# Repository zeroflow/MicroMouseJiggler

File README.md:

# MicroMouseJiggler
Arduino Pro Micro based mouse jiggler.

It's simple.

It has a button.
You push the button, it starts periodically jiggling your mouse cursor.
You push the button again, it stops jiggling your mouse cursor.

The button glows green when active, and flashes when moving the cursor.
If it's not active, the button glows red, but turns off after a minute.

The PCB is designed to be soldered on top of an Arduino Pro Micro.
To have an easy illuminated button, the lever is illuminated from below by a neopixel LED.

All pieces are designed with 3D printing in mind, but the tolerances are chosen very low for a good fit.

CAD source: https://a360.co/3dbTGTp

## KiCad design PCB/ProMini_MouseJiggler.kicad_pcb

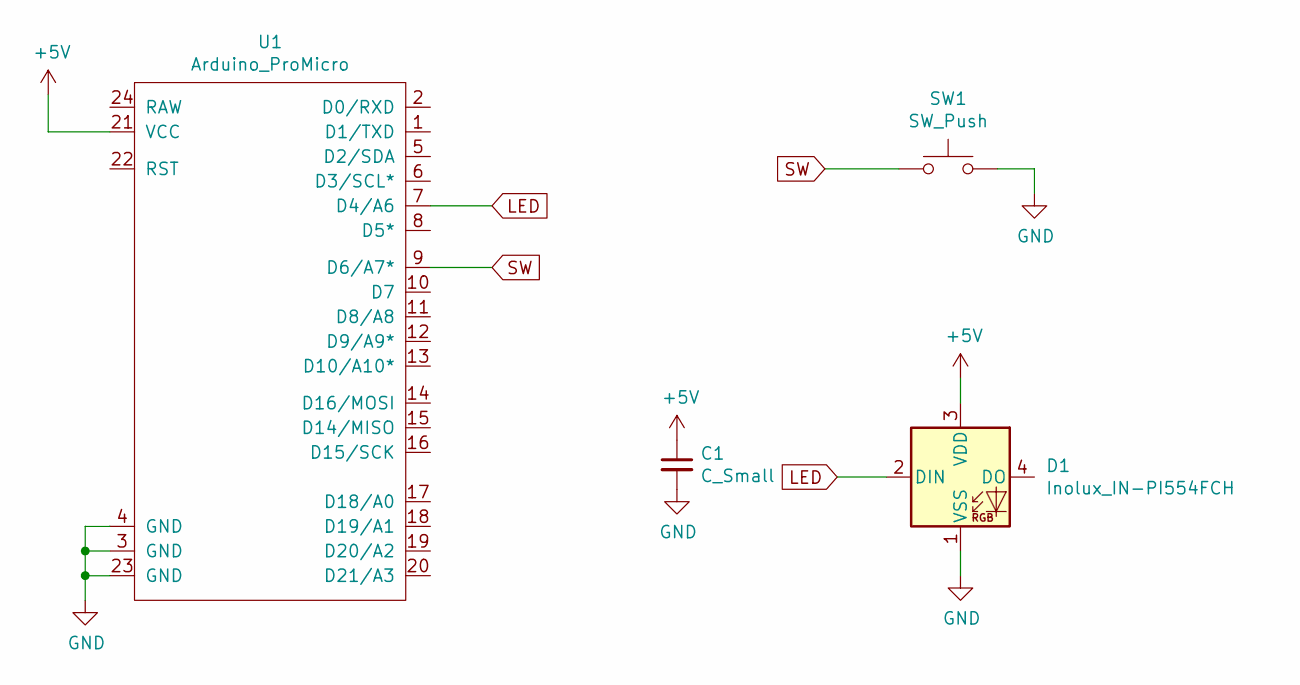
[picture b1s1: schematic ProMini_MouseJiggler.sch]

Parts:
C1: C_Small; C_0805_2012Metric_Pad1.18x1.45mm_HandSolder
D1: Inolux_IN-PI554FCH; LED_Inolux_IN-PI554FCH_PLCC4_5.0x5.0mm_P3.2mm
SW1: SW_Push; SW_Push_1P1T_NO_6x6mm_H9.5mm
U1: Arduino_ProMicro; Arduino Pro Micro

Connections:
+5V: C1.1, D1.3 (VDD), U1.21 (VCC)
GND: C1.2, D1.1 (VSS), SW1.2, U1.3 (GND), U1.4 (GND), U1.23 (GND)
LED: D1.2 (DIN), U1.7 (D4/A6)
SW: SW1.1, U1.9 (D6/A7*)

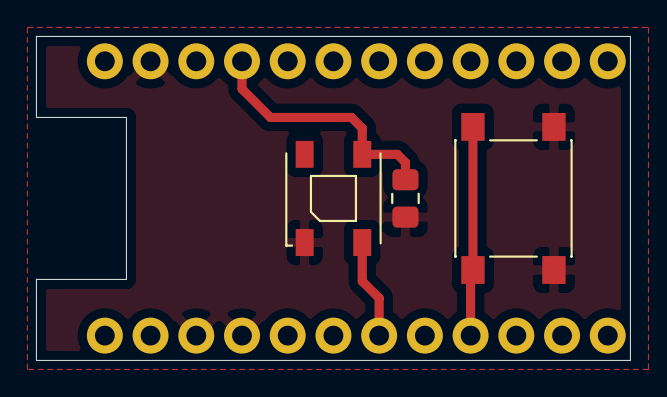
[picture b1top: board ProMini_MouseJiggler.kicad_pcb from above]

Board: 2 copper layers, 33.0 x 18.0 mm, 4 parts (0 on the bottom side), 4 nets.

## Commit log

2021-02-14 Initial Version
    Upload first working version
2021-02-14 Update README.md
    Replace 2nd picture with cut render
2021-02-14 Update README.md
    Add Description
2021-02-15 Update Mouse_Jiggler_Neopixel.ino
    Fix Color macro
    Brighter colors
